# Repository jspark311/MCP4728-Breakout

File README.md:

# MCP4728-Breakout

A breakout board for the Microchip i2c 4-channel DAC

------------------------

### What is in this repository:

**./doc**:  Location for documentation

**./KiCAD**:  Hardware design files

**./Arduino**:  Arduino driver

------------------------

Front | Back
:-------:|:------:
  |

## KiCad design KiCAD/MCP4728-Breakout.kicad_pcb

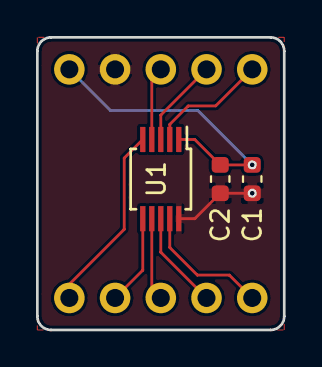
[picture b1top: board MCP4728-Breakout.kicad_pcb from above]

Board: 2 copper layers, 13.7 x 16.3 mm, 5 parts (0 on the bottom side), 10 nets.

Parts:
C1: 10uF; C_0603_1608Metric
C2: 1uF; C_0603_1608Metric
J1, J2: Conn_01x05_Male; PinHeader_1x05_P2.54mm_Vertical
U1: MCP4728; MSOP-10_3x3mm_P0.5mm

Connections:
/GND: C1.2, C2.2, J2.2, U1.10
/SCL: J2.5, U1.2
/SDA: J2.4, U1.3
/Vcc: C1.1, C2.1, J2.1, U1.1
/VoutA: J1.2, U1.6
/VoutB: J1.3, U1.7
/VoutC: J1.4, U1.8
/VoutD: J1.5, U1.9
/~BSY: J1.1, U1.5
/~LDAC: J2.3, U1.4

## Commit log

2019-12-10 Adding doc and PCB design files.
